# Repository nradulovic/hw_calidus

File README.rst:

.. contents:: Table of Contents
   :depth: 3

Introduction
============

This document shall describe rationales used to design and build audio
power amplifier using TDA7293 integrated circuit.

Architecture
============

The amplifier architecture consists of the following sections:

* Input section
* Output section
* Power amplifier with power supply and Control and Monitoring Unit (CMU)

Input section
=============

Input EMI suppression
---------------------

To protect the input from EMI we will use the following Zobel network:

.. code::
          o Positive input or negative input
          |
          |
        ----- Czi
        -----
          |
          |
         +-+  Rzi
         | |
         | |
         +-+
          |
         === Ground

For most input cables characteristic impedance falls in range between
50 and 100ohm impedance and we are using the 75ohm as the middle value. The
resistor Rzi is ``Rzi=75ohm`` and the capacitor Czi is ``Czi=220pF``.
This network should be placed right at the input connector, not on the
main amplifier PCB.

Also, a 100n X7R capacitor shall be placed between SGND and chassis right at the
input connector. This capacitor will shunt radio and other interfirence signal
into the Chassis Ground potential.

Input low-pass filter
---------------------

For input filter we choose the frequency between 300kHz and 400kHz.

.. code::

        +---+ Rlp1    +---+ Rlp2
    0---+   +----+----+   +---+---o Toward Amplifier IC block
        +---+    |    +---+   |
               ----- Clp1   ----- Clp2
               -----        -----
                 |            |
                === Ground   === Ground

Using the 2nd order CR low-pass filter calculator at URL:
*http://sim.okawa-denshi.jp/en/CRCRtool.php* we arrive at:

.. math::

    Rlp1 = 100 Ohm, Rlp2 = 100 Ohm

    Clp1 = 220pF,   Clp2 = 2.2nF

    fp1 = 352kHz

    fp2 = 14MHz

For more details please refer to: http://www.johnhearfield.com/RC/RC4.htm

The ground loop breaker resistor
--------------------------------

A ground loop breaker resistor is located between SGND and GNDPWR grounds. The
value of this resistor should be around 10 ohms.

Power amplifier
===============

Output EMI suppression
----------------------

Output network consists of upstream and downstream Zobel Network and of output
coil (``Ld``) with parallel, damping resistor (``Rd``). Upstream Zobel network 
provides a low-inductance load for the output stage at very high frequencies 
and allows high-frequency currents to circulate local to the output stage. The 
downstream Zobel network provides a good resistive termination right at the 
speaker terminals at high frequencies, helping to reduce RFI ingress and damp
resonances with, or reflections from, the speaker cables.
The output circuit is the following:

.. code::

    Ld
             xxx
        +---x   x   x---+
        |        xxx    |
        |               |
        |   +-------+   |
    o---+---|       |---+---o
    Vout    +-------+   |   Vspeaker
        Rd              |
                      ----- Cz2 = 100nF
                      -----
                        |
                        |
                       +-+  Rz1 = 10 Ohm
                       | |
                       | |
                       +-+
                        |
                       ===

The output coil ``Ld`` provides high frequency isolation of output load from 
output stage in TDA7293. The inductance value should be between 2uH up to 5uH.
Output shunt resistor should be between 2 and 5 Ohms. See
*Douglas Self - Audio Power Amplifier Design Handbook, 3rd Ed., Output networks, chapter 7*
for effect on power amplifier transfer function.

Paralleling multiple modules
----------------------------

Power dissipation
`````````````````

NOTE:

* Try to keep power dissipation to around 40W per IC package.

Fortunately, with music signals the power dissipation should be lower.
Effective power of music signal is about 2 to 10 times as smaller than
effective power of sinusoid signal. The power transformer is 200VA, meaning
that each channel gets 100VA of power.

Maximum voltages at:
 * Maximum ``Pdiss=50W`` for TDA7293.
 * Load phase is ``LoadPHI=60degrees``.
 * Including quiescent current dissipation.
 * Case temperature is 60C degrees.
 * Taking into account OPS SOA.

+-------------+-------------+-----------+--------------+
| Zload [ohm] | Vsupply [V] | Vdrop [V] | Pdiss [W]    |
+-------------+-------------+-----------+--------------+
| 16          | 33          | 2.2       | 31.4         |
+-------------+-------------+-----------+--------------+
| 12          | 29          | 2.3       | 31.6         |
+-------------+-------------+-----------+--------------+
| 8           | 25          | 2.5       | 34.2         |
+-------------+-------------+-----------+--------------+
| 6           | 22          | 2.6       | 34.7         |
+-------------+-------------+-----------+--------------+
| 4           | 19          | 2.9       | 37.4         |
+-------------+-------------+-----------+--------------+

This table tells us that if we want to drive 4ohm load at 33V we need 4 pieces
of TDA7293 in parallel. This is quite a number of ICs, but fortunately, the
table presumes that the power supply can produce constant 33V at continuous
load and the signal is sinusoid. This is not the case with unregulated power
supply and music signals. We have to take into account how much energy is
stored in power supply capacitors and how much will the transformer voltages
sag under these conditions and that music signal has much lower effective power
comparing to instantaneous power.

Transformer specification for TDA7293 amplifier is the following:
 * ``S=200VA``, power rating.
 * ``Usn1=24Veff``, first secondary nominal voltage.
 * ``Usn2=24Veff``, second secondary nominal voltage.
 * ``k=5%``, regulation.

Secondary internal resistance is:

.. math::

    Usu=Usn1*(1+(k/100))

    Isn=S/(Usn1+Usn2)

    Ri=(Usn1-Usu)/Isn

Using values from above we get:

.. math::

    Usu=24*(1+(5/100))=25.2Veff

    Isn=4.17Aeff

    Ri=288mOhm

The power supply section is using single bank of 10mF capacitors.

Gain value
----------

Using inverted topology since we want to reduce common mode distortion in the
input stage. But in case of TDA7293 IC it is not easy to use inverted topology
since the mute circuit is implemented on positive OPAMP input.

The equivalent gain circuit resistance needs to stay below 600ohms. This is so
because all noise measurements in data-sheet were done with 600ohms or 0ohms.

Using low feedback gain is preferred for several reasons:
 * there is more loop gain available to reduce the distortion
 * reduced outout noues
 * lower offset at output

Nominal gain is:

.. math::

    G=-Rf/Rg

Using E24 series of resistors:

+-----------+-----------+---------+
| Rf [Ohm]  | Rg [kOhm] | G [V/V] |
+-----------+-----------+---------+
| 510       |  7.5      | -14.7   |
+-----------+-----------+---------+
| *510*     |  *8.2*    | *-16.0* |
+-----------+-----------+---------+
| 510       |  9.1      | -17.8   |
+-----------+-----------+---------+
| 510       | 10.0      | -19.6   |
+-----------+-----------+---------+
| 510       | 11.0      | -21.5   |
+-----------+-----------+---------+

Using E24 series of resistors:

+-----------+-----------+---------+
| Rf [Ohm]  | Rg [kOhm] | G [V/V] |
+-----------+-----------+---------+
| 511       |  7.50     | -14.7   |
+-----------+-----------+---------+
| 511       |  7.87     | -15.4   |
+-----------+-----------+---------+
| *511*     |  *8.25*   | *-16.1* |
+-----------+-----------+---------+
| 511       |  8.66     | -16.9   |
+-----------+-----------+---------+
| 511       |  9.09     | -17.8   |
+-----------+-----------+---------+
| 511       |  9.53     | -18.6   |
+-----------+-----------+---------+
| 511       | 10.00     | -19.6   |
+-----------+-----------+---------+
| 511       | 10.50     | -20.5   |
+-----------+-----------+---------+
| 511       | 11.00     | -21.5   |
+-----------+-----------+---------+

Chosen values for E24 series:
 * Rf = 8.2kOhm
 * Rg = 510 Ohm

Chosen values for E48 series:
 * Rf = 8.25kOhm
 * Rg = 511 Ohm

Chosen values when using parallel E24 series (two resistor):
 * Rf = 16kOhm
 * Rg = 1kOhm

Chosen values when using parallel E48 series (two resistor):
 * Rf = 16.2kOhm
 * Rg = 1kOhm

Frequency compensation
----------------------

The TDA7293 data-sheet does not provide enough of relevant data in order to
model the IC in AC domain. Since we can't model it there are no optimizations
available for the negative feedback circuit. But we can safely assume that
there are high frequency poles present in the TDA7293 transfer function. For
this reason we will add a few ``pF`` to calculated lead compensation
capacitor below (see ``Cadd``).

Lead compensation
`````````````````

Equivalent feedback network with lead compensation circuit::

          o Vout
          |
          *------+
          |      |
         +-+ Rf  |
         | |   ----- Cf=Cl (+Csi, see Input pin capacitance compensation)
         | |   -----
         +-+     |
   Vf     |      |
    o-----*------+
          |
         +-+ Rg
         | |
         | |
         +-+
          |
          o Input

Resistors `Rf` and `Rg` are part of feedback network. Capacitor `Cf` is the
compensation capacitor. The transfer function of this network is given as:

.. math::

    Vf(s)=I(s)*Rg

    Vout(s)=I(s)*(Rf||Cl + Rg)=I(s)*(Rf/(1+s*Rf*Cl)+Rg)

    H(s)=Vf(s)/Vout(s)=(Rg/(Rf+Rg))*((1+s*Rf*Cl)/(1+s*Re*Cl))

Zero:

.. math::

    wz=1/(Rf*Cl)

Pole:

.. math::

    wp=1/(Re*Cl)

Where:

.. math::

    Re=Rf||Rg=Rf*Rg/(Rf+Rg)

Rough estimation is to put additional 1-3pF in parallel to ``Rf``.

.. math::

	Cadd = 3pF

Input pin capacitance compensation
``````````````````````````````````

Input pins have the following parasitic capacitances associated:

* Cdiff
* Cm
* Cstray

The TDA7293 data-sheet does not specify any parameter regarding parasitic
input capacitances. Voltage feedback OPAMPS usually have both differential and
common-mode input impedances specified. In the absence of any information, it
is safe to use the model given in the next figure:

.. code::

                   +----+ Zdiff
    +input o---+---|    |---+---o -input
               |   +----+   |
               |            |
              +-+ Zcm1     +-+ Zcm2
              | |          | |
              | |          | |
              +-+          +-+
               |            |
              ===          ===

We can use a rough estimation of values based on experience on using other 
audio FET OPAMPS, and typical values are around ``Cdiff=5pF``, ``Cm=4pF`` 
and ``Cstray=3pF``. All three equivalent capacitors are tied in parallel, 
so the total input capacitance becomes:

.. math::

    Cinput = Cdiff+Cm+Cstray=5pF+4pF+3pF=12pF

To mitigate this capacitance we can add capacitance `Csi` parallel to `Rf`
resistor. To compensate for this the following equation is applied:

.. math::

    Rf*Cf=Rg*Cinput

    Csi=Cinput*Rg/Rf=0.5pF

The final ``Cf`` value is:

.. math::

    Cf=Cl+Csi+Cadd=0+2+0.5=2.5pF

Any NP0 based capacitor around ``3pF`` will be good for this purpose.

Power supply
============

Power amplifier power supply
----------------------------

We are using dual symmetrical supplies from since dual secondaries. The high
voltage supplies are stabilized using LM317/LM337 regulators and are used to
feed input sections of TDA7293.

The low voltage supplies are supplied directly from reservoir capacitors. This
supply powers the high current, high power output sections of TDA7293.

By using dual and independent supplies for input sections and power sections we
can achieve very good PSRR results.

Before rectifier diodes a snubber RC circuit should be placed to decrease diode
switching impulse. Recommended values are ``Rsn = 1 Ohm``, ``Csn = 470nF``::

          o Vsupply
          |
          |
        ----- Csn = 470nF
        -----
          |
          |
         +-+  Rsn = 1 Ohm
         | |
         | |
         +-+
          |
         === Ground

This snubber may be placed near the IC power supply lines, too.

AC mains
--------

NOTE:
 * On case chassis there should be a safety ground screw just near at the input
   220V socket.

Control and Monitoring Unit
===========================

Amplifier controller will control and monitor two amplifiers. It has the
following components:

* Power supply undervoltage protection
* Power supply overvoltage protection
* Power supply imbalance protection
* Output DC offset protection
* Output clipping protection
* Over-temperature protection
* Over-current protection

Power supply undervoltage protection
------------------------------------

Power supply overvoltage protection
-----------------------------------

Power supply imbalance protection
---------------------------------

Output DC offset protection
---------------------------

Output clipping protection
--------------------------

Over-temperature protection
---------------------------

Over-current protection
-----------------------

Analog inputs
-------------

.. code::

                o  Vdd
                |
               +-+
               | | R2
               | |
         R1    +-+
        +---+   |
    o---|   |---+------+---o Analog output (to MCU ADC)
        +---+   |      |
    Analog     +-+     |
    Input      | | R3 --- C1
               | |    ---
               +-+     |
                |      |
               ===    ===

Enviromental parametars:

* Power supply: Vdd = 5V
* Analog output impedance: Rout <= 10k

Specification:

* Analog input range: Ain = +/-40V
* Analog input impedance: Rin >= 10k

Equations:
 (1) Since for 0V Ain we need 2.5V Aout: R2 = R1 || R3
 (2) Since we need gain 1/16 (5V/80V) we have: 16 = R1 / (R1 || R2 || R3)

This give as two equations with 3 unknowns:

.. math::

    (1 - Gain - 1)*G1 + G2 + G3 = 0

    Vref * G1 + Vref * G2 + (Vref - Vhigh) * G3 = 0

With Gain = 16, Vreg = 2.5V and Vhigh = 5V we have:

.. math::

    -15G1+G2+G3=0

    2.5G1+2.5G2-2.5G3=0

Start with G3 = 1/10:

.. math::

    -15G1+G2=-0.1

    2.5G1+2.5G2=0.25

    G1=1.25e+3 => R1=80kOhm

    G3=8.75e-2 => R2=11.43kOhm

One possibility is to have:

.. math::

    R1 = 110kOhm

    R2 = 10kOhm

    R3 = 11kOhm

This combination has Gain = 22

Monitor PIC18F46K40/PIC18F26K40 MCU pins
----------------------------------------

+-----------------------+---------------+-----------+-----------+---------------------------------------------------+
| # / Signal name       | Type          | 40 pin    | 28 pin    | Description                                       |
+-----------------------+---------------+-----------+-----------+---------------------------------------------------+
| 1. pa_vcc             | analog in     | RD0       |           | Measures the VCC voltage                          |
+-----------------------+---------------+-----------+-----------+---------------------------------------------------+
| 2. pa_vee             | analog in     | RD1       |           | Measures the VEE voltage                          |
+-----------------------+---------------+-----------+-----------+---------------------------------------------------+
| 3. pa_ope             | analog in     | RA6       | RA6       | Measures Output Positive Envelope (Both channels) |
+-----------------------+---------------+-----------+-----------+---------------------------------------------------+
| 4. pa_one             | analog in     | RA7       | RA7       | Measures Output Negative Envelope (Both channels) |
+-----------------------+---------------+-----------+-----------+---------------------------------------------------+
| 5. pa_oal             | analog in     | RA2       | RA2       | Measures Output Average Left                      |
+-----------------------+---------------+-----------+-----------+---------------------------------------------------+
| 6. pa_oar             | analog in     | RA4       | RA4       | Measures Output Average Right                     |
+-----------------------+---------------+-----------+-----------+---------------------------------------------------+
| 7. pc_ol              | analog/comp in| RA0       | RA0       | Compares Output Left impedance                    |
+-----------------------+---------------+-----------+-----------+---------------------------------------------------+
| 8. pc_or              | analog/comp in| RA1       | RA1       | Compares Output Right impedance                   |
+-----------------------+---------------+-----------+-----------+---------------------------------------------------+
| 9. pc_ref             | analog/comp in| RA3       | RA3       | Comparator reference voltage                      |
+-----------------------+---------------+-----------+-----------+---------------------------------------------------+
| 10. pc_i2c_scl        | i2c scl       | RC3       | RC3       | Sensor network SCL                                |
+-----------------------+---------------+-----------+-----------+---------------------------------------------------+
| 11. pc_i2c_sda        | i2c sda       | RC4       | RC4       | Sensor network SDA                                |
+-----------------------+---------------+-----------+-----------+---------------------------------------------------+
| 12. pc_uart_rx        | uart rx       | RC7       | RC7       | Service terminal RX (from PIC perspective)        |
+-----------------------+---------------+-----------+-----------+---------------------------------------------------+
| 13. pc_uart_tx        | uart tx       | RC6       | RC6       | Service terminal TX (from PIC perspective)        |
+-----------------------+---------------+-----------+-----------+---------------------------------------------------+
| 14. po_comp_en        | dig out       | RA5       | RA5       | Enable comparator current sources                 |
+-----------------------+---------------+-----------+-----------+---------------------------------------------------+
| 15. po_ctrl_power     | dig out       | RB1       | RB1       | Control power relay                               |
+-----------------------+---------------+-----------+-----------+---------------------------------------------------+
| 16. po_ctrl_pbypass   | dig out       | RB2       | RB2       | Control power bypass relay                        |
+-----------------------+---------------+-----------+-----------+---------------------------------------------------+
| 17. po_ctrl_mute      | dig out       | RB3       | RB3       | Control mute relay                                |
+-----------------------+---------------+-----------+-----------+---------------------------------------------------+
| 18. po_ctrl_enable    | dig out       | RB4       | RB4       | Control power amplifier enable                    |
+-----------------------+---------------+-----------+-----------+---------------------------------------------------+
| 19. po_ind_power_a    | dig out       | RB5       | RB5       | Indicator power/status LED, pin A                 |
+-----------------------+---------------+-----------+-----------+---------------------------------------------------+
| 20. po_ind_power_b    | dig out       | RD2       |           | Indicator power/status LED, pin B                 |
+-----------------------+---------------+-----------+-----------+---------------------------------------------------+
| 21. po_ind_overload   | dig out       | RB6       | RB6       | Indicator overload LED                            |
+-----------------------+---------------+-----------+-----------+---------------------------------------------------+
| 22. po_status         | dig out       | RB7       | RB7       | Status LED on board                               |
+-----------------------+---------------+-----------+-----------+---------------------------------------------------+
| 23. pi_key_power      | dig in        | RB0       | RB0       | Power key                                         |
+-----------------------+---------------+-----------+-----------+---------------------------------------------------+
| 24. pi_key_mute       | dig in        | RC5       | RC5       | Mute key                                          |
+-----------------------+---------------+-----------+-----------+---------------------------------------------------+
| 25. pi_det_ac_power   | dig in        | RC0       | RC0       | AC power detection                                |
+-----------------------+---------------+-----------+-----------+---------------------------------------------------+
| 26. pi_det_overload   | dig in        | RC1       | RC1       | Overload detection                                |
+-----------------------+---------------+-----------+-----------+---------------------------------------------------+
| 27. pi_det_signal     | dig in        | RC2       | RC2       | Signal detection                                  |
+-----------------------+---------------+-----------+-----------+---------------------------------------------------+
| 28. pi_cfg_power      | dig in        | RD3       |           | Configure power control mode                      |
+-----------------------+---------------+-----------+-----------+---------------------------------------------------+
| 29. pi_cfg_ac_power   | dig in        | RD4       |           | Configure AC power detection mode                 |
+-----------------------+---------------+-----------+-----------+---------------------------------------------------+
| 30. pi_cfg_impedance  | dig in        | RD5       |           | Configure Impedance monitoring mode               |
+-----------------------+---------------+-----------+-----------+---------------------------------------------------+
| 31. pi_cfg_sensors    | dig in        | RD6       |           | Configure sensors mode                            |
+-----------------------+---------------+-----------+-----------+---------------------------------------------------+
| 32.                   |               | RD7       |           |                                                   |
+-----------------------+---------------+-----------+-----------+---------------------------------------------------+
| 33.                   |               | RE0       |           |                                                   |
+-----------------------+---------------+-----------+-----------+---------------------------------------------------+
| 34.                   |               | RE1       |           |                                                   |
+-----------------------+---------------+-----------+-----------+---------------------------------------------------+
| 35.                   |               | RE2       |           |                                                   |
+-----------------------+---------------+-----------+-----------+---------------------------------------------------+

Hardware configurations
-----------------------

Power control mode

* 0 - Disabled, always on
* 1 - Enabled, wait for Power on event

AC power detection mode:

* 0 - Disabled, AC always present
* 1 - Enabled, AC detect on

Impedance monitoring mode:

* 0 - Disabled, always allow power on
* 1 - Enabled, dissallow power on when impedance is out of minimal limit

Sensors mode:

* 0 - Disabled, all temperature sensors are ignored
* 1 - Enabled, read all temperature sensors

Software configurations
-----------------------

Power supply:

* nominal value: 20V
* minimal value: 15V
* maximum value: 25V
* imbalance value: 10V
* bypass time: 500ms
* post bypass time: 500ms
* mode, same as HW configuration 1

Clipping detector:

* clipping min voltage 4: 5
* clipping min voltage 8: 3
* hold off: 1000ms
* timeout to mute: 10s
* timeout to shutdown: 20s
* mode:

  * 0 - Disabled,
  * 1 - Enabled

AC detector:

* num of cycles missing: 4
* mode, same as HW configuration 2

Impedance detector:

* mode, same as HW configuration 3

Temperature detector:

* mode

Chassis
=======

Component height
----------------

Power supply capacitors on amplifier boards:

* 30mm (10mF)

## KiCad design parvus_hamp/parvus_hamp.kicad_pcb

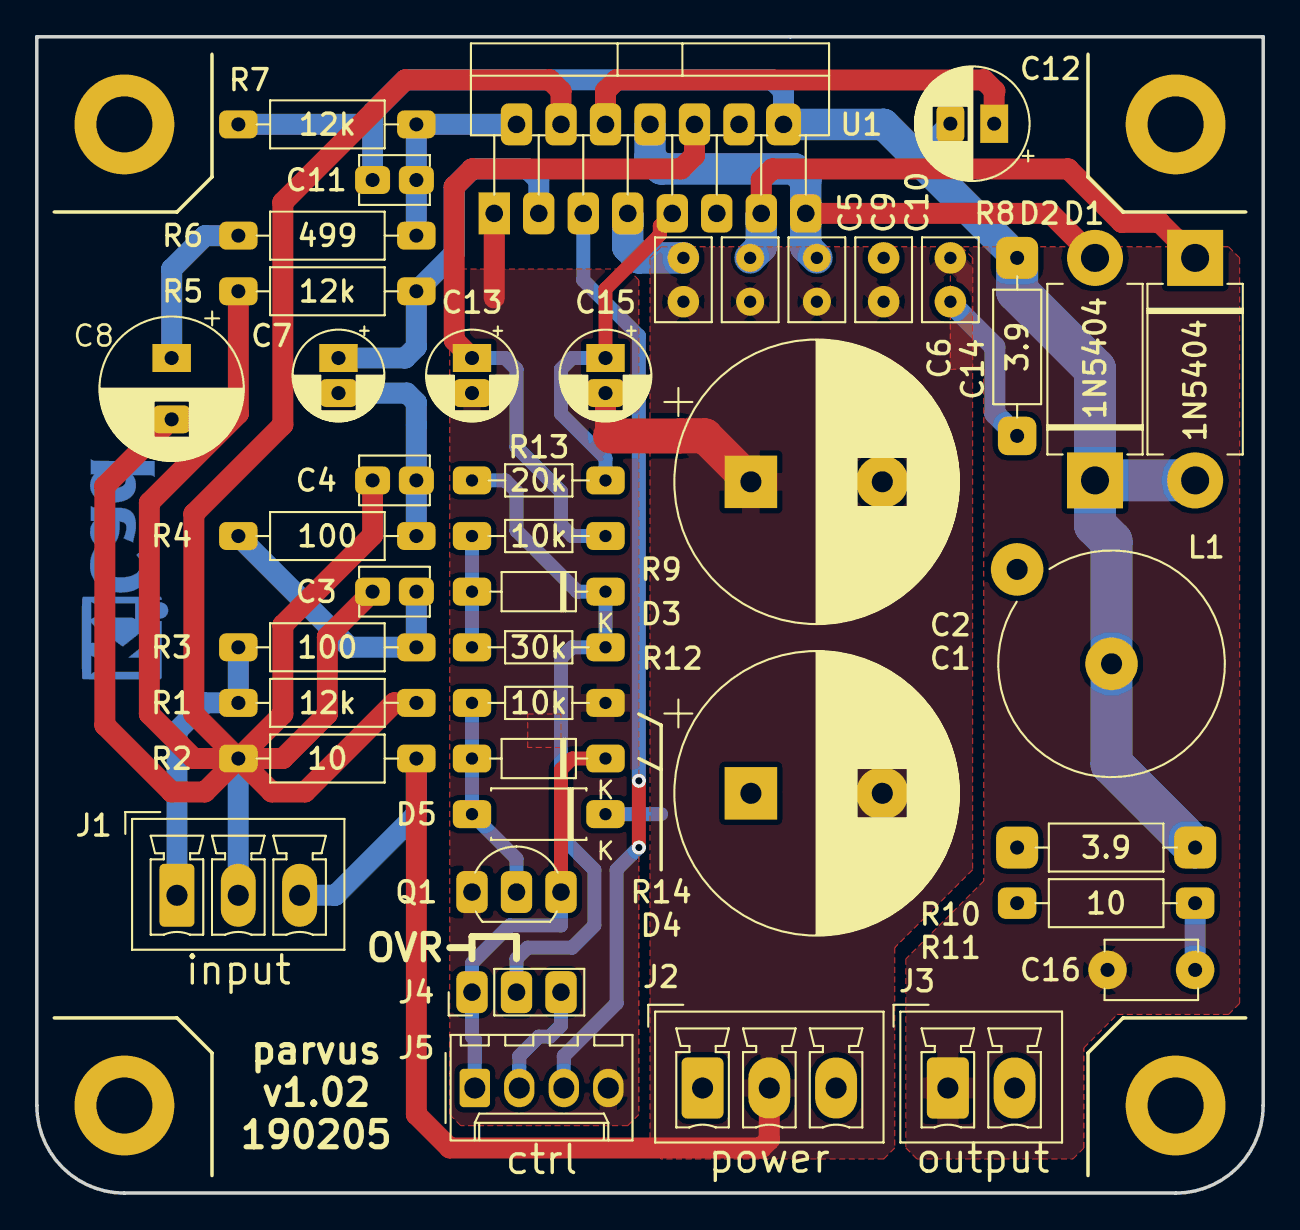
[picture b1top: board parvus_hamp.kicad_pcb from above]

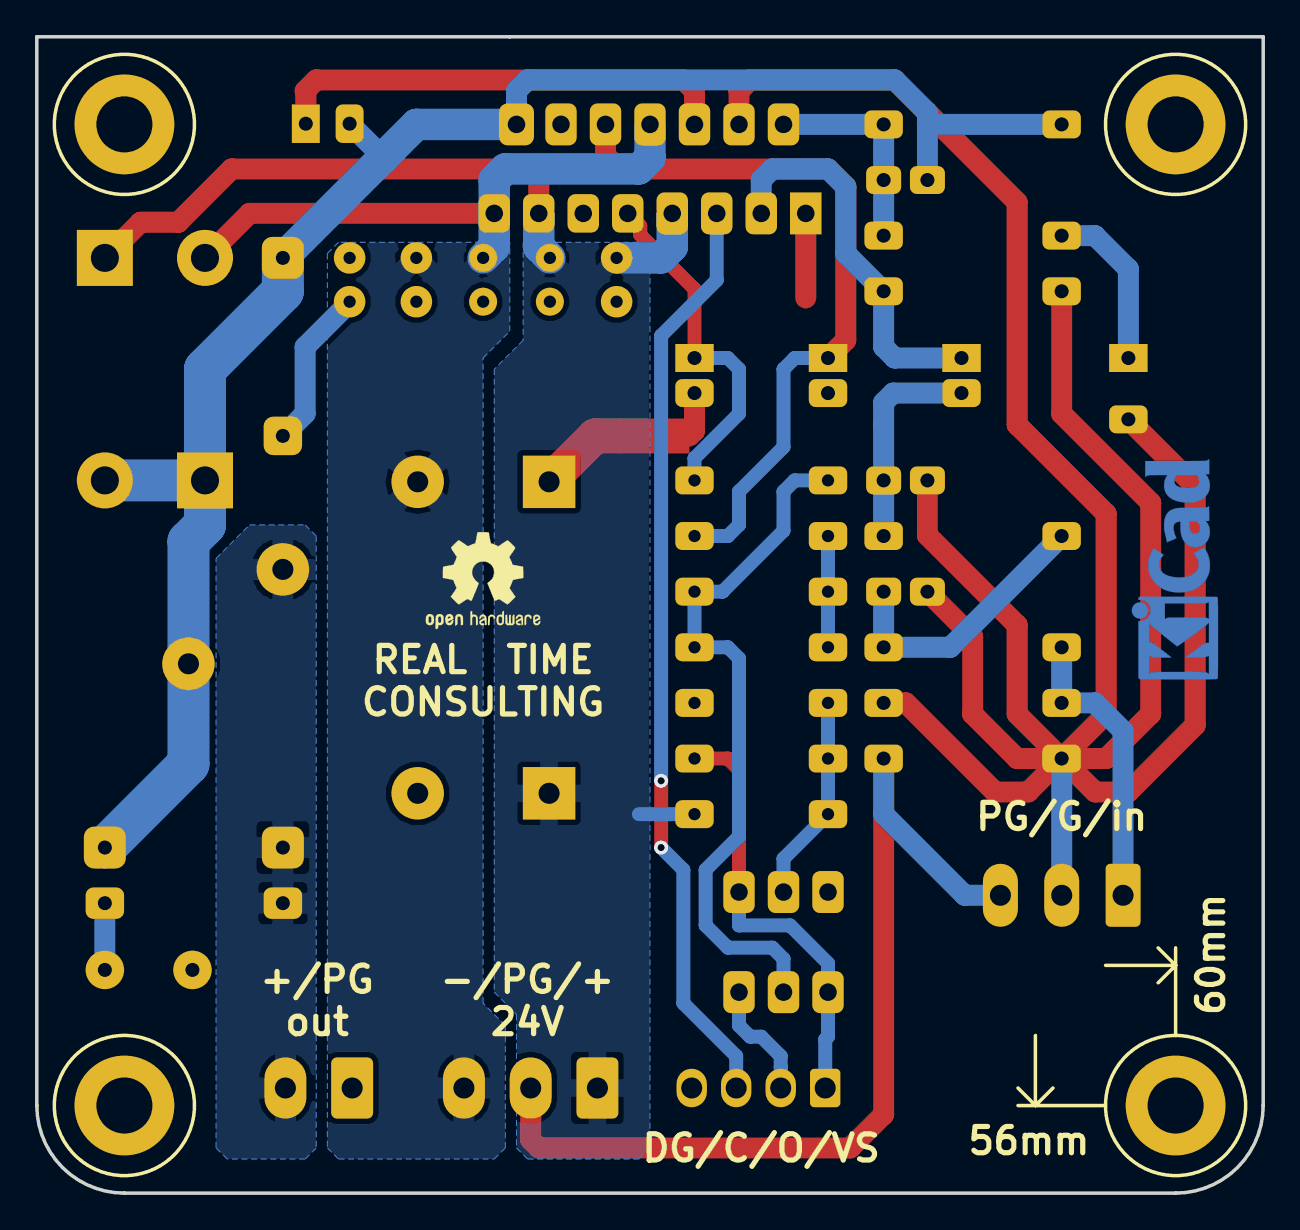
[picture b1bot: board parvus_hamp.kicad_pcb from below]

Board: 2 copper layers, 70.0 x 66.0 mm, 50 parts (2 on the bottom side), 24 nets.

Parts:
C1, C2: 2m2; CP_Radial_D16.0mm_P7.50mm
C3, C4: 220p; C_Disc_D3.8mm_W2.6mm_P2.50mm
C5, C6: 220n; C_Rect_L4.6mm_W3.0mm_P2.50mm_MKS02_FKP02
C7: 22u; CP_Radial_D5.0mm_P2.00mm
C8: 470u; CP_Radial_D8.0mm_P3.50mm
C9, C10: 22n; C_Rect_L4.6mm_W3.0mm_P2.50mm_MKS02_FKP02
C11: 3p3; C_Disc_D3.8mm_W2.6mm_P2.50mm
C12: 47u; CP_Radial_D6.3mm_P2.50mm
C13, C15: 10u; CP_Radial_D5.0mm_P2.00mm
C14: 100n; C_Rect_L4.6mm_W3.0mm_P2.50mm_MKS02_FKP02
C16: 100n; C_Disc_D5.1mm_W3.2mm_P5.00mm
D1, D2: 1N5404; D_DO-201AD_P12.70mm_Horizontal
D3, D4: 1N4148; D_DO-35_SOD27_P7.62mm_Horizontal
D5: 1N5246B; D_DO-41_SOD81_P7.62mm_Horizontal
J1: input; PhoenixContact_MCV_1,5_3-G-3.5_1x03_P3.50mm_Vertical
J2: power; PhoenixContact_MCV_1,5_3-G-3.81_1x03_P3.81mm_Vertical
J3: output; PhoenixContact_MCV_1,5_2-G-3.81_1x02_P3.81mm_Vertical
J4: ctrl_override; PinHeader_1x03_P2.54mm_Vertical
J5: ctrl; Molex_KK-254_AE-6410-04A_1x04_P2.54mm_Vertical
L1: 4u; L_Axial_L20.3mm_D12.7mm_P7.62mm_Vertical_Vishay_IHA-201
LOGO1: Kicad_Logo; KiCad-Logo_5mm_Copper
LOGO2: OSHW Logo; OSHW-Logo2_7.3x6mm_SilkScreen
MK1, MK2, MK3, MK4: Mounting_Hole; MountingHole_3.2mm_M3_ISO7380_Pad
NT1: Net-Tie_2; NetTie-2_SMD_Pad2.0mm
Q1: BC556B; TO-92L_Inline_Wide
R1, R5, R7: 12k; R_Axial_DIN0207_L6.3mm_D2.5mm_P10.16mm_Horizontal
R2, R11: 10; R_Axial_DIN0207_L6.3mm_D2.5mm_P10.16mm_Horizontal
R3, R4: 100; R_Axial_DIN0207_L6.3mm_D2.5mm_P10.16mm_Horizontal
R6: 499; R_Axial_DIN0207_L6.3mm_D2.5mm_P10.16mm_Horizontal
R8, R10: 3.9; R_Axial_DIN0207_L6.3mm_D2.5mm_P10.16mm_Horizontal
R9, R14: 10k; R_Axial_DIN0204_L3.6mm_D1.6mm_P7.62mm_Horizontal
R12: 30k; R_Axial_DIN0204_L3.6mm_D1.6mm_P7.62mm_Horizontal
R13: 20k; R_Axial_DIN0204_L3.6mm_D1.6mm_P7.62mm_Horizontal
U1: TDA7293; TO-220-15_P2.54x2.54mm_StaggerOdd_Lead4.58mm_Vertical

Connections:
+pwvs: C1.1, C5.1, C9.1, D1.1, D5.1, J2.1, U1.7, U1.13
-pwvs: C2.2, C6.2, C10.2, D2.2, J2.3, U1.8, U1.15
/input: J1.1, R1.2, R3.2
/mute: C13.1, R9.2, U1.10
/out: J3.2, L1.2, R10.1, R11.1
/preout: C11.2, C12.2, D1.2, D2.1, L1.1, R7.2, R8.1, R10.2, U1.14
/sgnd: C3.2, C4.2, C8.2, J1.2, R1.1, R2.1, R5.1, U1.4
/stby: C15.1, R13.2, U1.9
GNDD: C13.2, C15.2, J5.4, NT1.2, Q1.1, R14.1, U1.1
GNDPWR: C1.2, C2.1, C5.2, C6.1, C9.2, C10.1, C14.2, C16.2, J1.3, J2.2, J3.1, NT1.1, R2.2
unnamed: C3.1, R3.1, R4.2
unnamed: C4.1, C7.2, R4.1
unnamed: C7.1, R5.2, U1.3
unnamed: C8.1, R6.2
unnamed: C11.1, R6.1, R7.1, U1.2
unnamed: C12.1, U1.6
unnamed: C14.1, R8.2
unnamed: C16.1, R11.2
unnamed: D3.1, J4.2, R12.1, R13.1
unnamed: D3.2, R9.1, R12.2
unnamed: D4.1, J4.1, J5.1, Q1.3
unnamed: D4.2, D5.2, Q1.2, R14.2
unnamed: J4.3, J5.2
unnamed: J5.3, U1.5

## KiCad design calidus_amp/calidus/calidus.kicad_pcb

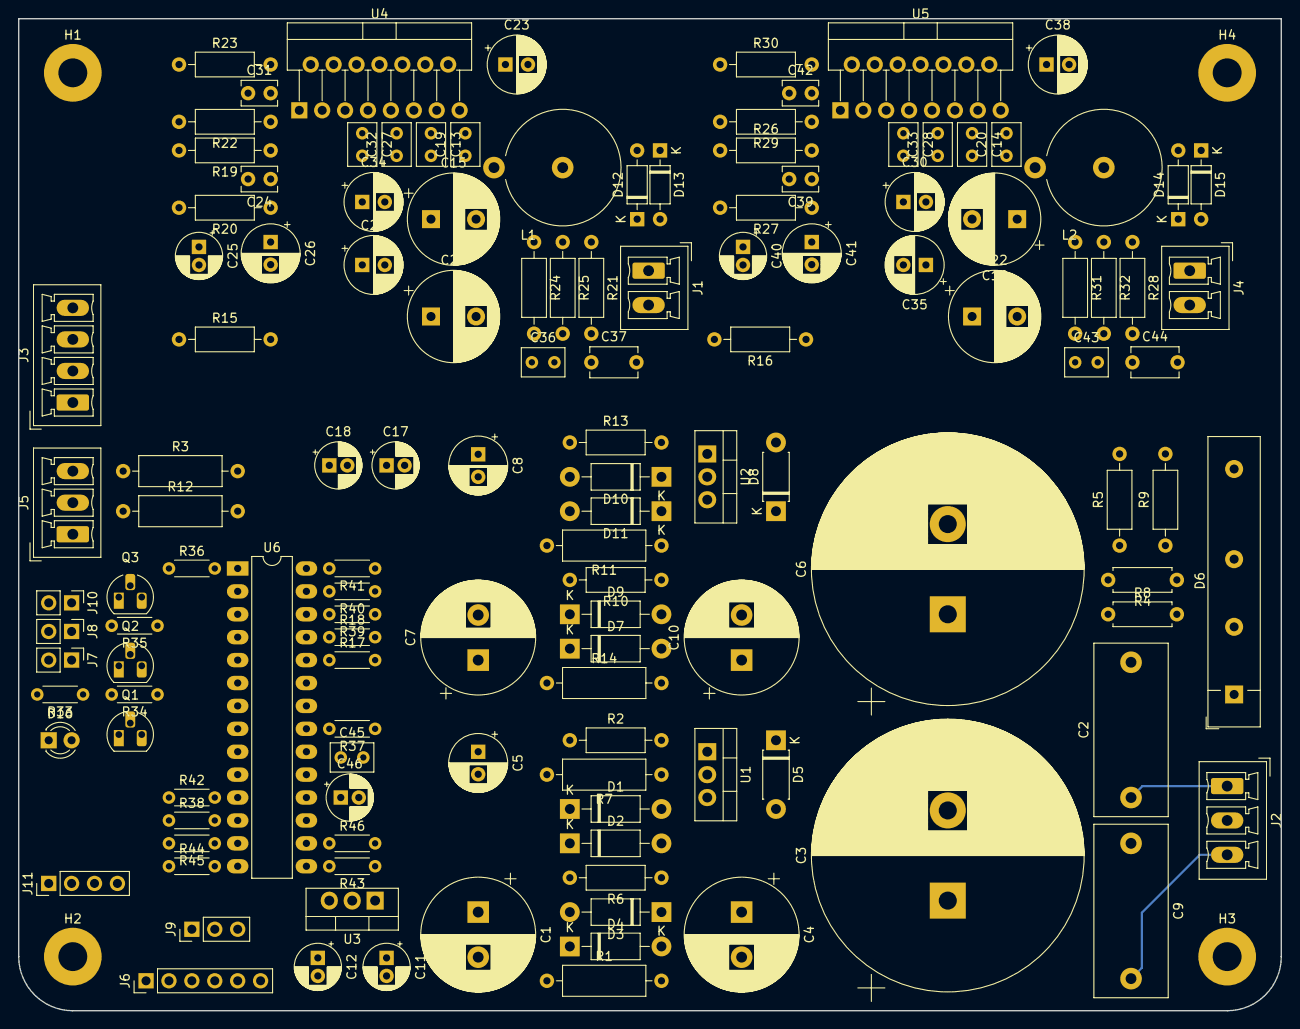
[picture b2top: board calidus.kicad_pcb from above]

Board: 4 copper layers, 140.0 x 110.0 mm, 134 parts (0 on the bottom side), 70 nets.

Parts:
C1, C4, C7, C10: 470u; CP_Radial_D12.5mm_P5.00mm
C2, C9: 220n; C_Rect_L19.0mm_W8.0mm_P15.00mm_MKS4
C3, C6: 10m; CP_Radial_D30.0mm_P10.00mm_SnapIn
C5, C8, C23, C29, C30, C34, C35, C38: 47u; CP_Radial_D6.3mm_P2.50mm
C11, C12, C17, C18, C25, C40, C46: 10u; CP_Radial_D5.0mm_P2.00mm
C13, C14, C19, C20, C27, C28, C32, C33, C36, C43, C45: 100n; C_Rect_L4.6mm_W3.0mm_P2.50mm_MKS02_FKP02
C15, C16, C21, C22: 220u; CP_Radial_D10.0mm_P5.00mm
C24, C39: 220p; C_Disc_D3.8mm_W2.6mm_P2.50mm
C26, C41: 220u; CP_Radial_D6.3mm_P2.50mm
C31, C42: 3p3; C_Disc_D3.8mm_W2.6mm_P2.50mm
C37, C44: 100n; C_Disc_D5.1mm_W3.2mm_P5.00mm
D1, D11: BZX85C20; D_DO-41_SOD81_P10.16mm_Horizontal
D2, D3, D4, D7, D9, D10: 1N4007; D_DO-41_SOD81_P10.16mm_Horizontal
D5, D8: MBR1100RLG; D_DO-41_SOD81_P7.62mm_Horizontal
D6: D_Bridge_+A-A; Diode_Bridge_32.0x5.6x17.0mm_P10.0mm_P7.5mm
D12, D13, D14, D15: 1N5404; D_DO-35_SOD27_P7.62mm_Horizontal
D16: LED; LED_D3.0mm
H1, H2, H3, H4: Mounting; MountingHole_3.2mm_M3_Pad
J1: left_out; PhoenixContact_MCV_1,5_2-G-3.81_1x02_P3.81mm_Vertical
J2: power; PhoenixContact_MCV_1,5_3-G-3.81_1x03_P3.81mm_Vertical
J3: input; PhoenixContact_MCV_1,5_4-G-3.5_1x04_P3.50mm_Vertical
J4: right_out; PhoenixContact_MCV_1,5_2-G-3.81_1x02_P3.81mm_Vertical
J5: prevs; PhoenixContact_MCV_1,5_3-G-3.5_1x03_P3.50mm_Vertical
J6: icsp; PinHeader_1x06_P2.54mm_Vertical
J7: mute_key; PinHeader_1x02_P2.54mm_Vertical
J8: led_overload; PinHeader_1x02_P2.54mm_Vertical
J9: service; PinHeader_1x03_P2.54mm_Vertical
J10: led_power; PinHeader_1x02_P2.54mm_Vertical
J11: sense_bus; PinHeader_1x04_P2.54mm_Vertical
L1, L2: 4u; L_Axial_L20.3mm_D12.7mm_P7.62mm_Vertical_Vishay_IHA-201
Q1, Q2, Q3: Q_NPN_CBE; TO-92_HandSolder
R1, R3, R12, R14: 47; R_Axial_DIN0309_L9.0mm_D3.2mm_P12.70mm_Horizontal
R2, R13: 120; R_Axial_DIN0207_L6.3mm_D2.5mm_P10.16mm_Horizontal
R4, R8: 1; R_Axial_DIN0207_L6.3mm_D2.5mm_P7.62mm_Horizontal
R5, R9: 10k; R_Axial_DIN0207_L6.3mm_D2.5mm_P10.16mm_Horizontal
R6, R10: 30k; R_Axial_DIN0207_L6.3mm_D2.5mm_P10.16mm_Horizontal
R7, R11: 3k3; R_Axial_DIN0309_L9.0mm_D3.2mm_P12.70mm_Horizontal
R15, R16, R25, R32: 10; R_Axial_DIN0207_L6.3mm_D2.5mm_P10.16mm_Horizontal
R17, R18: 20k; R_Axial_DIN0204_L3.6mm_D1.6mm_P5.08mm_Horizontal
R19, R23, R26, R30: 12k; R_Axial_DIN0207_L6.3mm_D2.5mm_P10.16mm_Horizontal
R20, R22, R27, R29: 499; R_Axial_DIN0207_L6.3mm_D2.5mm_P10.16mm_Horizontal
R21, R24, R28, R31: 3.9; R_Axial_DIN0207_L6.3mm_D2.5mm_P10.16mm_Horizontal
R33, R34, R35: 620; R_Axial_DIN0204_L3.6mm_D1.6mm_P5.08mm_Horizontal
R36, R37, R38, R39, R40, R41, R45, R46: 10k; R_Axial_DIN0204_L3.6mm_D1.6mm_P5.08mm_Horizontal
R42: 100k; R_Axial_DIN0204_L3.6mm_D1.6mm_P5.08mm_Horizontal
R43, R44: 2k4; R_Axial_DIN0204_L3.6mm_D1.6mm_P5.08mm_Horizontal
U1: LM317; TO-220-3_Vertical
U2: LM337; TO-220-3_Vertical
U3: L7805; TO-220-3_Vertical
U4, U5: TDA7293; TO-220-15_P2.54x2.54mm_StaggerOdd_Lead4.58mm_Vertical
U6: PIC18F26K42-I/SP; DIP-28_W7.62mm_LongPads

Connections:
+pdvs: C12.1, C45.1, C46.1, D16.2, J6.2, J7.1, J8.1, J10.1, J11.4, R36.1, R37.1, R38.1, R43.1, R44.1, U3.3, U6.20
+prevs: J5.3, R3.1
+pwvs: C3.1, C11.1, C13.1, C14.1, C15.1, C16.1, D5.2, D6.1, D12.1, D14.1, R3.2, R5.1, U3.1, U4.13, U5.13
+vs: C5.1, C27.1, C28.1, C29.1, C30.1, D1.2, D2.2, D5.1, R2.1, U1.2, U4.7, U5.7
-prevs: J5.1, R12.1
-pwvs: C6.2, C19.2, C20.2, C21.2, C22.2, D6.3, D8.1, D13.2, D15.2, R9.2, R12.2, U4.15, U5.15
-vs: C8.2, C32.2, C33.2, C34.2, C35.2, D8.2, D10.1, D11.1, R13.2, U2.3, U4.8, U5.8
/Control and Monitoring Unit/ac_in: C9.2, D6.2, J2.3, R14.2, R42.1
/Control and Monitoring Unit/i2c_scl: J11.2, R44.2, U6.14
/Control and Monitoring Unit/i2c_sda: J11.3, R43.2, U6.15
/Control and Monitoring Unit/icspclk: J6.5, R40.2, U6.27
/Control and Monitoring Unit/icspdat: J6.4, R41.2, U6.28
/Control and Monitoring Unit/icsprst: J6.1, R36.2, U6.1
/Control and Monitoring Unit/mute: R17.1, U6.24
/Control and Monitoring Unit/mute_key: J7.2, R46.1, U6.16
/Control and Monitoring Unit/overload: R38.2, U4.5, U5.5, U6.12
/Control and Monitoring Unit/overload_led: J8.2, R34.2
/Control and Monitoring Unit/power_led: J10.2, R33.2
/Control and Monitoring Unit/stby: R18.1, U6.25
/Control and Monitoring Unit/uart_rx: J9.3, U6.18
/Control and Monitoring Unit/uart_tx: J9.2, U6.17
/pamp/in_l: C25.2, J3.4
/pamp/in_r: C40.2, J3.2
/pamp/out_l: J1.1, L1.2, R21.1, R25.1
/pamp/out_r: J4.1, L2.2, R28.1, R32.1
/psupply/pri_hi: C2.1, D6.4, J2.1, R1.2
Earth_Protective: C3.2, C4.2, C5.2, C6.1, C7.1, C8.1, C11.2, C12.2, C13.2, C14.2, C15.2, C16.2, C17.2, C18.2, C19.1, C20.1, C21.1, C22.1, C27.2, C28.2, C29.2, C30.2, C32.1, C33.1, C34.1, C35.1, C36.2, C37.2, C43.2, C44.2, C45.2, C46.2, D4.2, D7.1, J1.2, J2.2, J4.2, J5.2, J6.3, J9.1, J11.1, Q1.3, Q2.3, Q3.3, R4.2, R5.2, R6.2, R7.2, R8.1, R9.1, R10.1, R11.1, R15.2, R16.2, R45.2, R46.2, U3.2, U4.1, U5.1, U6.8, U6.19
unnamed: C1.1, D3.2, D4.1
unnamed: C1.2, R1.1
unnamed: C2.2, R4.1
unnamed: C4.1, D1.1, D2.1, D3.1, R6.1, U1.3
unnamed: C7.2, D9.2, D10.2, D11.2, R10.2, U2.2
unnamed: C9.1, R8.2
unnamed: C10.1, R14.1
unnamed: C10.2, D7.2, D9.1
unnamed: C17.1, R18.2, U4.9, U5.9
unnamed: C18.1, R17.2, U4.10, U5.10
unnamed: C23.1, U4.6
unnamed: C23.2, U4.12
unnamed: C24.1, R19.1, R20.1, U4.3
unnamed: C25.1, R20.2
unnamed: C26.1, R22.2
unnamed: C31.1, D12.2, D13.1, L1.1, R21.2, R23.2, R24.1, U4.14
unnamed: C31.2, R22.1, R23.1, U4.2
unnamed: C36.1, R24.2
unnamed: C37.1, R25.2
unnamed: C38.1, U5.6
unnamed: C38.2, U5.12
unnamed: C39.1, R26.1, R27.1, U5.3
unnamed: C40.1, R27.2
unnamed: C41.1, R29.2
unnamed: C42.1, D14.2, D15.1, L2.1, R28.2, R30.2, R31.1, U5.14
unnamed: C42.2, R29.1, R30.1, U5.2
unnamed: C43.1, R31.2
unnamed: C44.1, R32.2
unnamed: D16.1, R35.2
unnamed: Q1.1, R33.1
unnamed: Q1.2, R39.1
unnamed: Q2.1, R34.1
unnamed: Q2.2, R40.1
unnamed: Q3.1, R35.1
unnamed: Q3.2, R41.1
unnamed: R2.2, R7.1, U1.1
unnamed: R11.2, R13.1, U2.1
unnamed: R37.2, U6.21
unnamed: R39.2, U6.26
unnamed: R42.2, U6.11
unnamed: R45.1, U6.13
gnds_l: C24.2, C26.2, J3.3, R15.1, R19.2, U4.4
gnds_r: C39.2, C41.2, J3.1, R16.1, R26.2, U5.4

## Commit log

2019-01-08 Added PSU capacitor models.
2019-01-11 Created new project and schematics.
2019-01-13 Upgraded power supply
    Using new power supply design with 3pin linear regulator
2019-01-22 Update of the schematic
2019-01-22 Cleanup
2019-01-22 Daily update
2019-01-23 Added description of Amplifier Controller in README.rst
2019-01-23 Updated component designators and finished CMU
2019-01-24 Updated schematic and footprinted Rybicon capacitors
2019-01-24 Annotated the schematic
2019-01-25 WIP: Updated footprints
2019-01-29 WIP: component footprint assignment.
2019-01-29 WIP: Component placement on PCB
2019-01-29 WIP: Removed unnecessary heatsinks
2019-01-29 WIP: Component placement
2019-01-30 Fixed formatting errors.
2019-01-30 WIP: Component placement and footpring assignment
2019-01-30 WIP: Component placement and footprint assignement
    - Finished all capacitors
    - Finished all ICs
2019-01-30 WIP: Minor placement adjustements
2019-01-30 WIP: Component placement.
2019-01-31 Updated README.rst formatting
2020-04-22 Added parallel TDA7293 implementation.
2021-08-31 chore: project update
